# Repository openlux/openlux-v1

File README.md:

This is the first version of this camera and had a few small design issues, these will be fixed in v2.

# openlux

openlux is an open source design for an astrophotography camera designed around the KAI-11002 CCD sensor.

### Hardware specifications

* 4-layer PCB

* KAI-11002 CCD sensor
  * 4008x2672 resolution
  * 43.3mm diagonal size
  * 9um pixels
  * Interline transfer
  * Electronic shutter

* AD9826 ADC
  * Correlated double sampling
  * 16-bit

* ATmega328P + FT2232H
  * High speed USB 2.0 (480Mb/s)

### Sample photo

* 32x 5min lights (2hrs 40mins total), 16x darks, 16x flats, 16x dark flats
* AT65EDQ + HEQ5
* ST80 & ASI174MM for guiding

### PCB render

### Photos

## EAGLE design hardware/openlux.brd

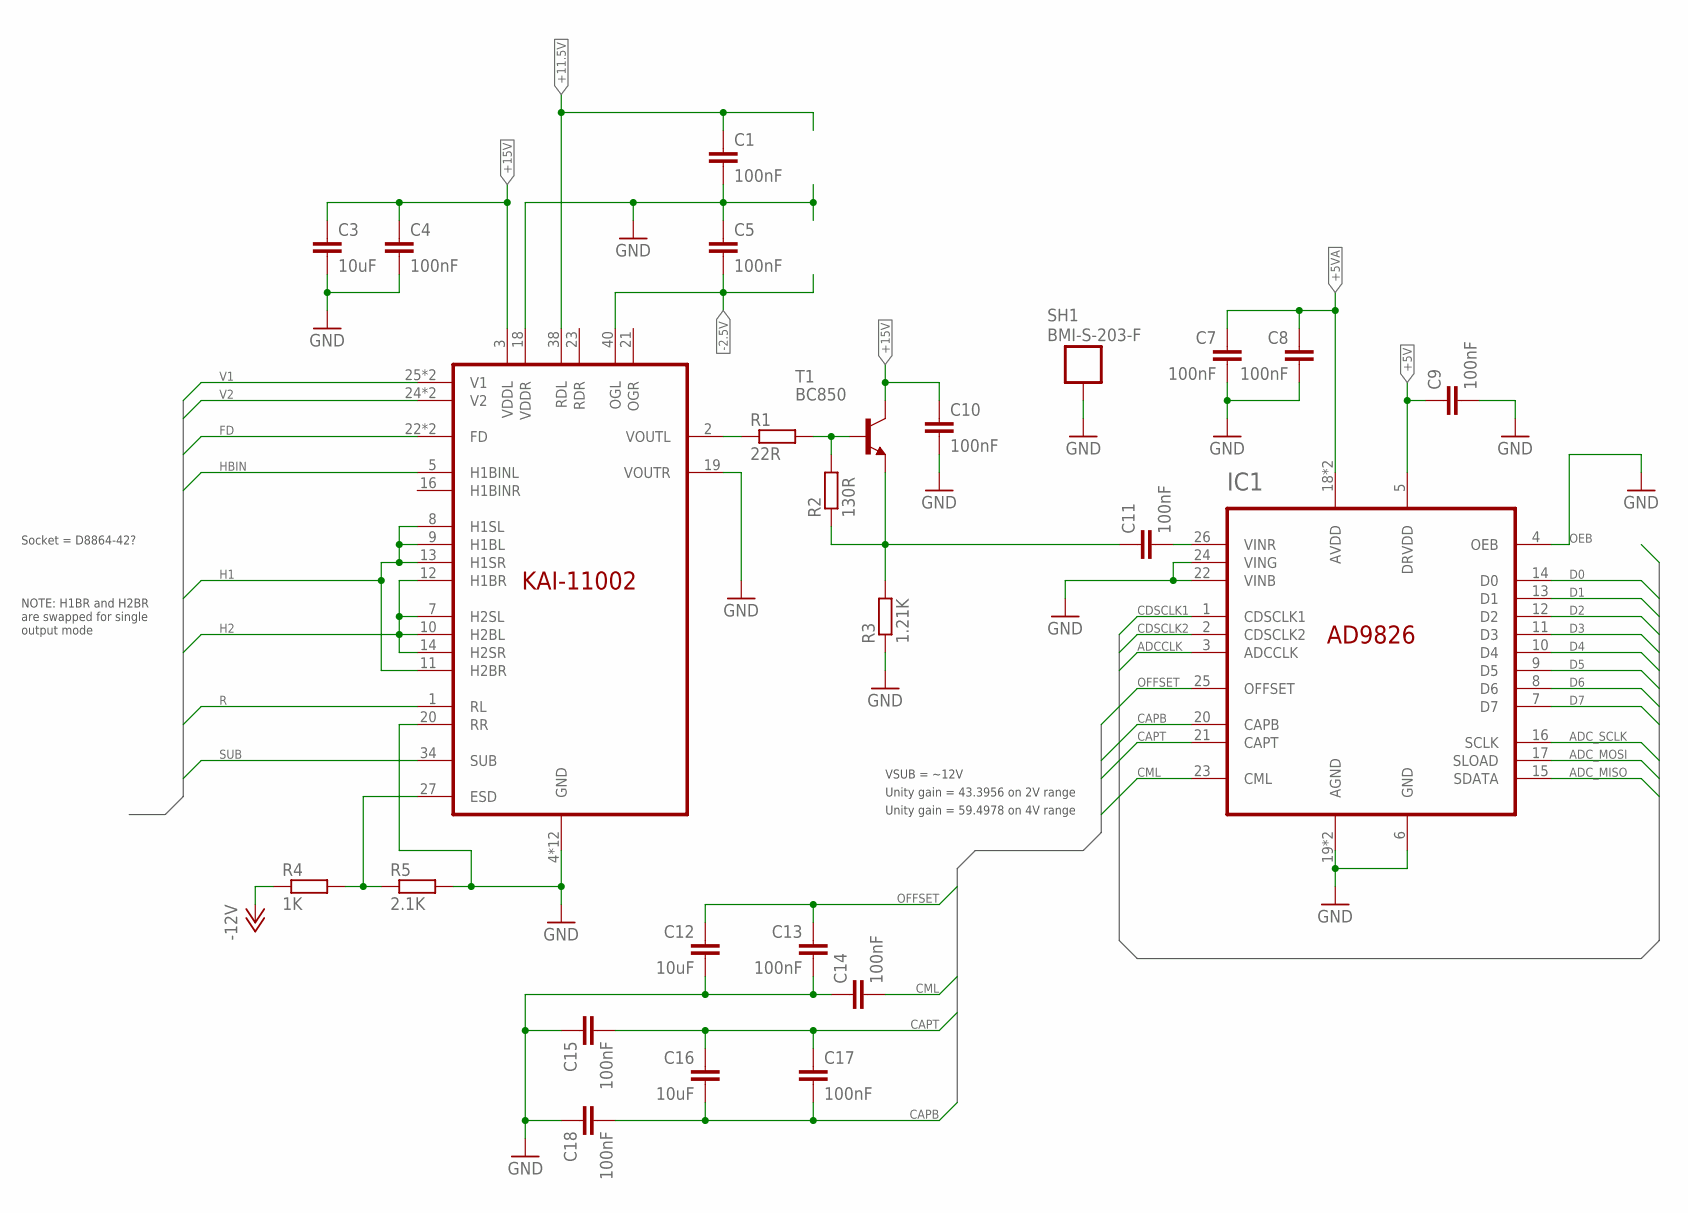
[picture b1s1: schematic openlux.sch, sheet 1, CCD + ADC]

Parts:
C1, C4, C5, C7, C8, C9, C10, C11, C13, C14, C15, C17, C18: 100nF; 0603
C3, C12, C16: 10uF; 0805
IC1: AD9826; SSOP28
IS1: KAI-11002
R1: 22R; 0603
R2: 130R; 0603
R3: 1.21K; 0603
R4: 1K; 0603
R5: 2.1K; 0603
SH1: BMI-S-203-F
T1: BC850; SOT23

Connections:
+5V: C9.1, IC1.5 (DRVDD); also elsewhere on the board
+5VA: C7.1, C8.1, IC1.18 (AVDD), IC1.28 (AVDD); also elsewhere on the board
+11.5V: C1.1, IS1.38 (RDL); also elsewhere on the board
+15V: C3.1, C4.1, C10.1, IS1.3 (VDDL), T1.3 (C); also elsewhere on the board
-2.5V: C5.2, IS1.40 (OGL); also elsewhere on the board
-12V: R4.1; also elsewhere on the board
ADCCLK: IC1.3 (ADCCLK); also elsewhere on the board
ADC_MISO: IC1.15 (SDATA)
ADC_MOSI: IC1.17 (SLOAD)
ADC_SCLK: IC1.16 (SCLK)
CAPB: C16.2, C17.2, C18.2, IC1.20 (CAPB)
CAPT: C15.2, C16.1, C17.1, IC1.21 (CAPT)
CDSCLK1: IC1.1 (CDSCLK1); also elsewhere on the board
CDSCLK2: IC1.2 (CDSCLK2); also elsewhere on the board
CML: C14.2, IC1.23 (CML)
D0: IC1.14 (D0); also elsewhere on the board
D1: IC1.13 (D1); also elsewhere on the board
D2: IC1.12 (D2); also elsewhere on the board
D3: IC1.11 (D3); also elsewhere on the board
D4: IC1.10 (D4); also elsewhere on the board
D5: IC1.9 (D5); also elsewhere on the board
D6: IC1.8 (D6); also elsewhere on the board
D7: IC1.7 (D7); also elsewhere on the board
FD: IS1.22 (FD), IS1.39 (FD); also elsewhere on the board
GND: C1.2, C3.2, C4.2, C5.1, C7.2, C8.2, C9.2, C10.2, C12.2, C13.2, C14.1, C15.1, C18.1, IC1.4 (OEB), IC1.6 (GND), IC1.19 (AGND), IC1.22 (VINB), IC1.24 (VING), IC1.27 (AGND), IS1.4 (GND), IS1.6 (GND), IS1.15 (GND), IS1.17 (GND), IS1.18 (VDDR), IS1.19 (VOUTR), IS1.20 (RR), IS1.26 (GND), IS1.28 (GND), IS1.29 (GND), IS1.30 (GND), IS1.31 (GND), IS1.32 (GND), IS1.33 (GND), IS1.35 (GND), R3.1, R5.2, SH1.P$1, SH1.P$2, SH1.P$3, SH1.P$4, SH1.P$5, SH1.P$6, SH1.P$7, SH1.P$8, SH1.P$9, SH1.P$10, SH1.P$11, SH1.P$12, SH1.P$13, SH1.P$14, SH1.P$15, SH1.P$19, SH1.P$20; also elsewhere on the board
H1: IS1.8 (H1SL), IS1.9 (H1BL), IS1.11 (H2BR), IS1.13 (H1SR); also elsewhere on the board
H2: IS1.7 (H2SL), IS1.10 (H2BL), IS1.12 (H1BR), IS1.14 (H2SR); also elsewhere on the board
HBIN: IS1.5 (H1BINL); also elsewhere on the board
unnamed: R1.2, R2.2, T1.1 (B)
unnamed: C11.2, IC1.26 (VINR)
unnamed: IS1.2 (VOUTL), R1.1
OFFSET: C12.1, C13.1, IC1.25 (OFFSET)
R: IS1.1 (RL); also elsewhere on the board
SUB: IS1.34 (SUB); also elsewhere on the board
V1: IS1.25 (V1), IS1.37 (V1); also elsewhere on the board
V2: IS1.24 (V2), IS1.36 (V2); also elsewhere on the board
VESD: IS1.27 (ESD), R4.2, R5.1
VOUT: C11.1, R2.1, R3.2, T1.2 (E)

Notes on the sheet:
NOTE: H1BR and H2BR are swapped for single output mode
Unity gain = 43.3956 on 2V range
Unity gain = 59.4978 on 4V range
Socket = D8864-42?
VSUB = ~12V

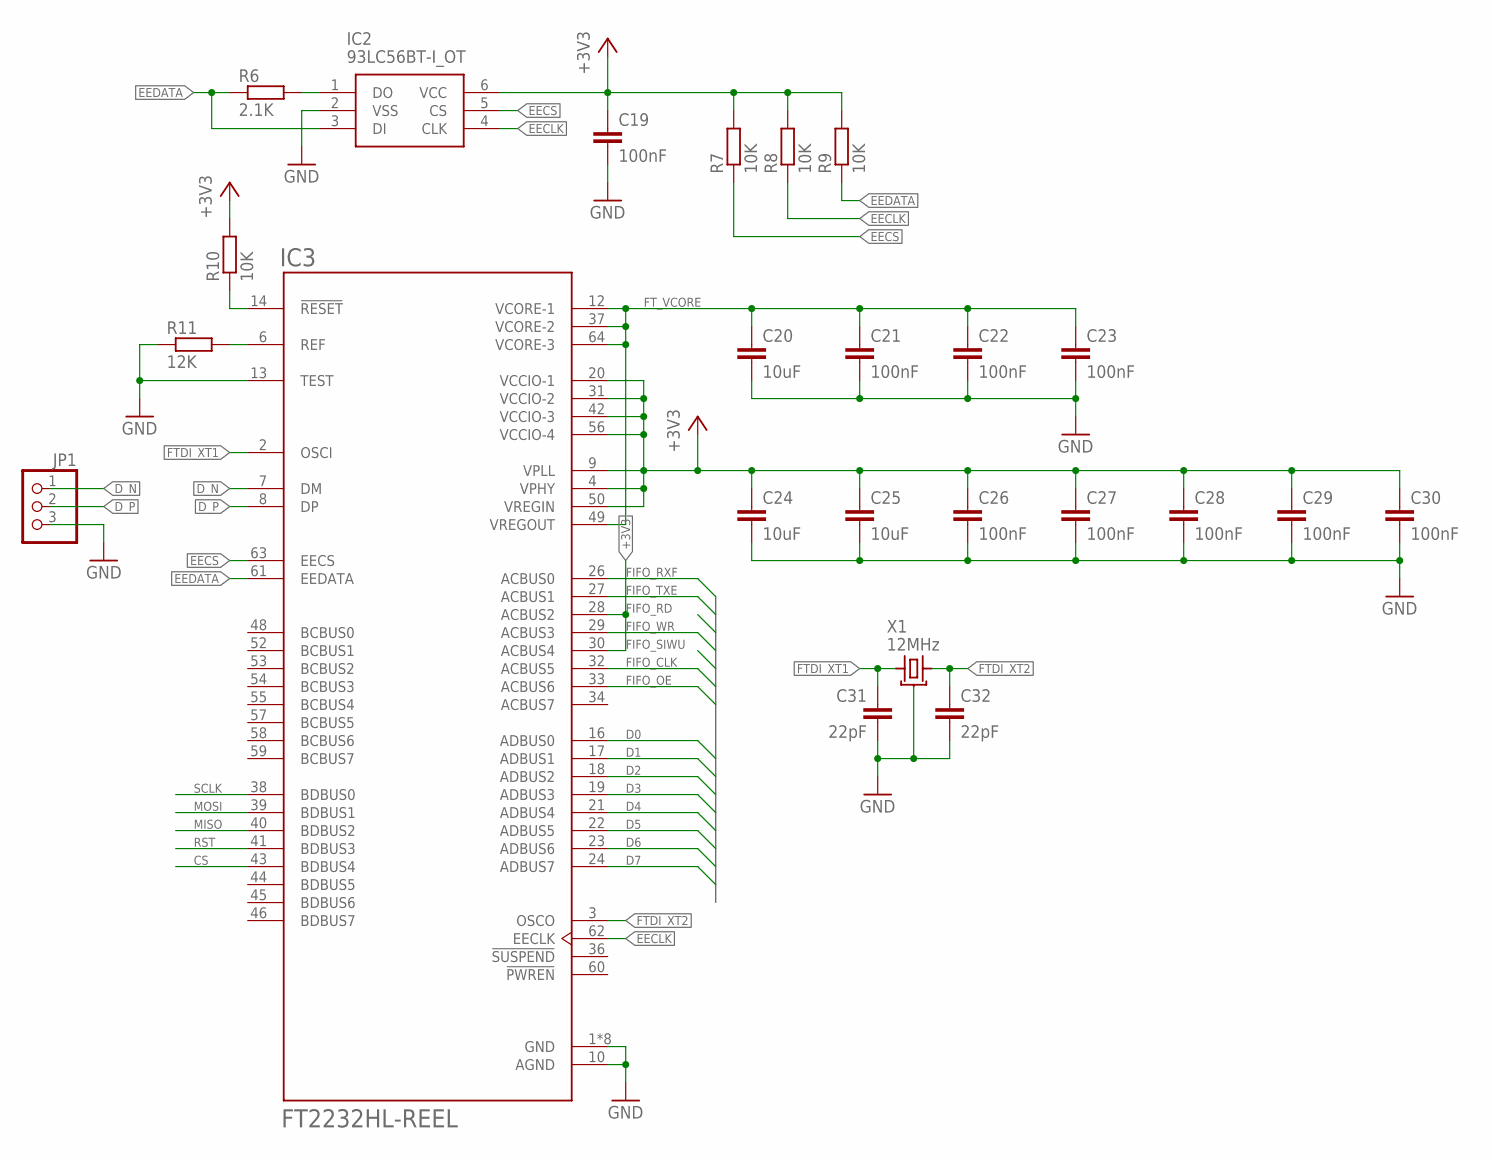
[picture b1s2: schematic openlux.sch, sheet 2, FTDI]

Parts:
C19, C21, C22, C23, C26, C27, C28, C29, C30: 100nF; 0603
C20, C24, C25: 10uF; 0805
C31, C32: 22pF; 0603
IC2: 93LC56BT-I_OT; SOT95P270X145-6N
IC3: FT2232HL-REEL; QFP50P1200X1200X160-64N
JP1: PINHD-1X3; 1X03
R6: 2.1K; 0603
R7, R8, R9, R10: 10K; 0603
R11: 12K; 0603
X1: 12MHz; 3.2X2.5_4

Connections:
+3V3: C19.1, C24.1, C25.1, C26.1, C27.1, C28.1, C29.1, C30.1, IC2.6 (VCC), IC3.4 (VPHY), IC3.9 (VPLL), IC3.20 (VCCIO-1), IC3.28 (ACBUS2), IC3.30 (ACBUS4), IC3.31 (VCCIO-2), IC3.42 (VCCIO-3), IC3.50 (VREGIN), IC3.56 (VCCIO-4), R7.2, R8.2, R9.2, R10.2; also elsewhere on the board
CS: IC3.43 (BDBUS4); also elsewhere on the board
D0: IC3.16 (ADBUS0); also elsewhere on the board
D1: IC3.17 (ADBUS1); also elsewhere on the board
D2: IC3.18 (ADBUS2); also elsewhere on the board
D3: IC3.19 (ADBUS3); also elsewhere on the board
D4: IC3.21 (ADBUS4); also elsewhere on the board
D5: IC3.22 (ADBUS5); also elsewhere on the board
D6: IC3.23 (ADBUS6); also elsewhere on the board
D7: IC3.24 (ADBUS7); also elsewhere on the board
D_N: IC3.7 (DM), JP1.1
D_P: IC3.8 (DP), JP1.2
EECLK: IC2.4 (CLK), IC3.62 (EECLK), R8.1
EECS: IC2.5 (CS), IC3.63 (EECS), R7.1
EEDATA: IC2.3 (DI), IC3.61 (EEDATA), R6.1, R9.1
FIFO_CLK: IC3.32 (ACBUS5)
FIFO_OE: IC3.33 (ACBUS6)
FIFO_RXF: IC3.26 (ACBUS0)
FIFO_TXE: IC3.27 (ACBUS1); also elsewhere on the board
FIFO_WR: IC3.29 (ACBUS3); also elsewhere on the board
FTDI_XT1: C31.1, IC3.2 (OSCI), X1.P$1 (XT1)
FTDI_XT2: C32.1, IC3.3 (OSCO), X1.P$3 (XT2)
FT_VCORE: C20.1, C21.1, C22.1, C23.1, IC3.12 (VCORE-1), IC3.37 (VCORE-2), IC3.49 (VREGOUT), IC3.64 (VCORE-3)
GND: C19.2, C20.2, C21.2, C22.2, C23.2, C24.2, C25.2, C26.2, C27.2, C28.2, C29.2, C30.2, C31.2, C32.2, IC2.2 (VSS), IC3.1 (GND), IC3.5 (GND), IC3.10 (AGND), IC3.11 (GND), IC3.13 (TEST), IC3.15 (GND), IC3.25 (GND), IC3.35 (GND), IC3.47 (GND), IC3.51 (GND), JP1.3, R11.1, X1.P$2 (GND), X1.P$4 (GND); also elsewhere on the board
MISO: IC3.40 (BDBUS2); also elsewhere on the board
MOSI: IC3.39 (BDBUS1); also elsewhere on the board
unnamed: IC3.6 (REF), R11.2
unnamed: IC2.1 (DO), R6.2
unnamed: IC3.14 (!RESET), R10.1
RST: IC3.41 (BDBUS3); also elsewhere on the board
SCLK: IC3.38 (BDBUS0); also elsewhere on the board

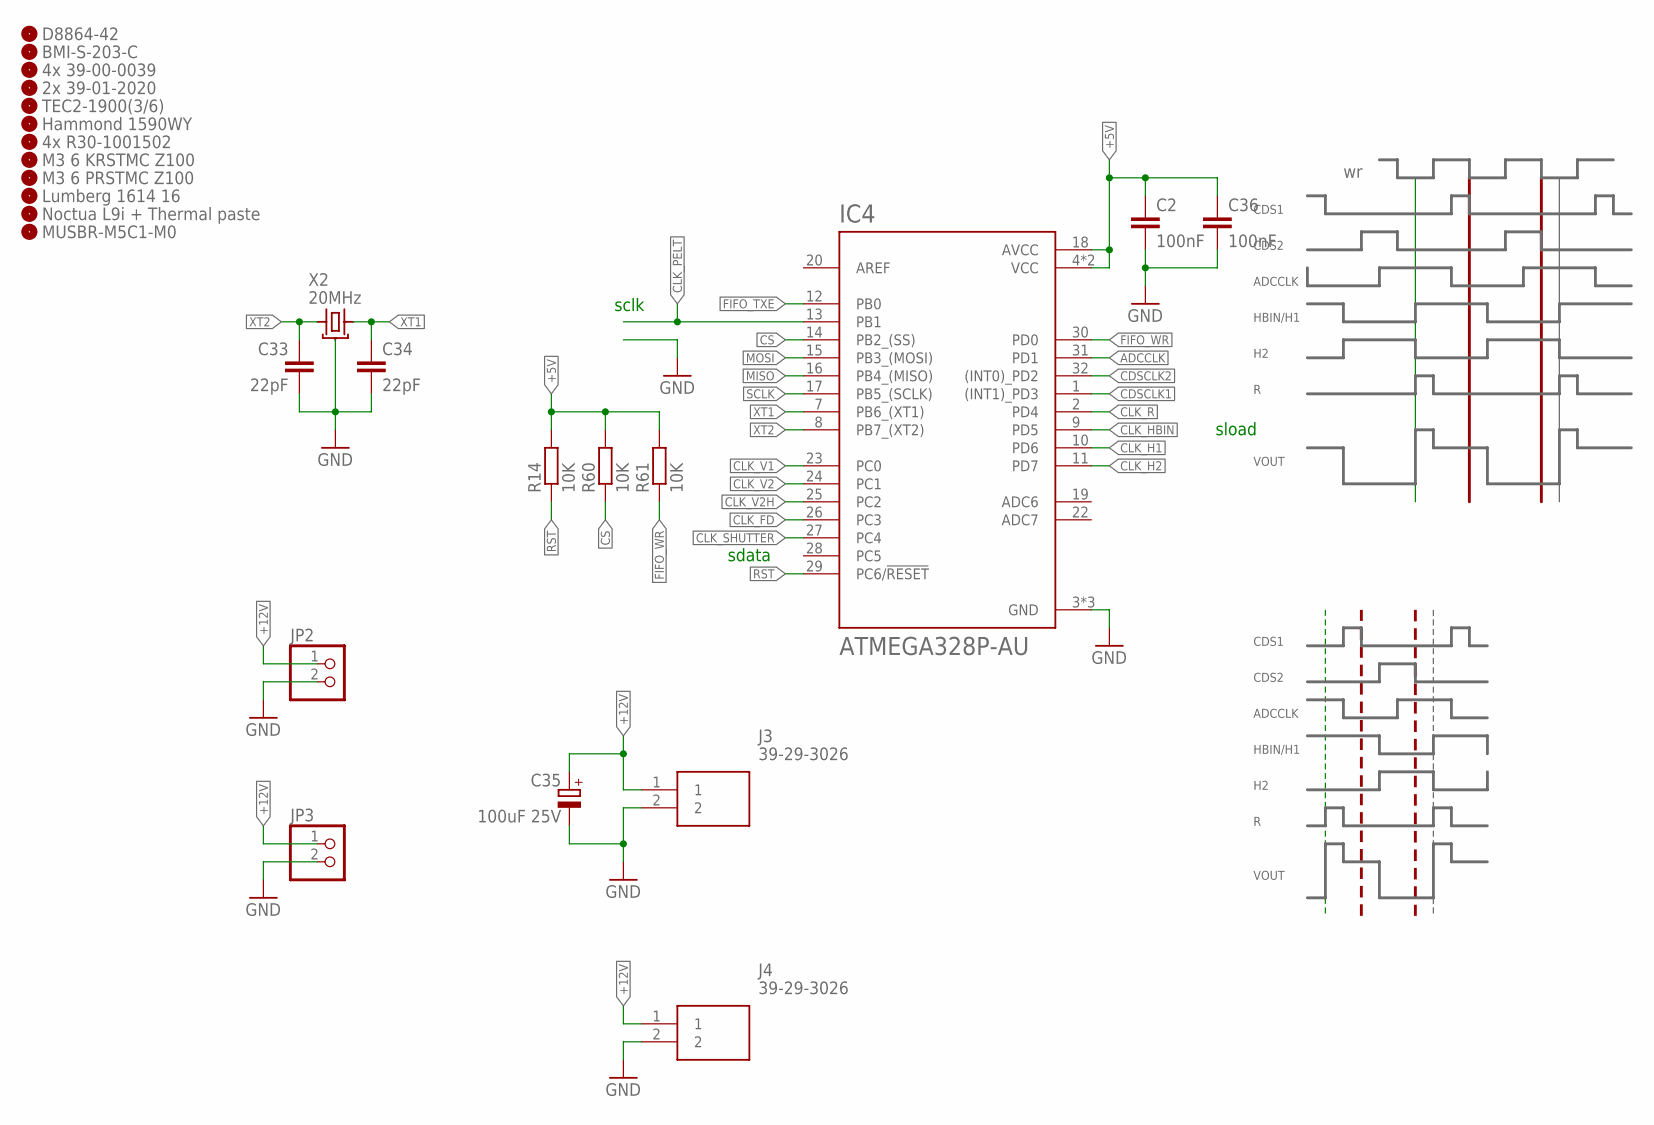
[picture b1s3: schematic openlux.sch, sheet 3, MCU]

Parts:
C2, C36: 100nF; 0603
C33, C34: 22pF; 0603
C35: 100uF 25V; E2,5-6
EXTRA1: 4x R30-1001502; EMPTY
EXTRA2: Hammond 1590WY; EMPTY
EXTRA3: M3 6 KRSTMC Z100; EMPTY
EXTRA4: M3 6 PRSTMC Z100; EMPTY
EXTRA5: TEC2-1900(3/6); EMPTY
EXTRA6: 2x 39-01-2020; EMPTY
EXTRA7: 4x 39-00-0039; EMPTY
EXTRA8: Lumberg 1614 16; EMPTY
EXTRA9: Noctua L9i + Thermal paste; EMPTY
EXTRA10: MUSBR-M5C1-M0; EMPTY
EXTRA11: BMI-S-203-C; EMPTY
EXTRA12: D8864-42; EMPTY
IC4: ATMEGA328P-AU; QFP80P900X900X120-32N
J3, J4: 39-29-3026; SHDR2W125P0X550_1X2_960X540X13
JP2: PINHD-1X2; 1X02
JP3: PINHD-1X2/90; 1X02/90
R14, R60, R61: 10K; 0603
X2: 20MHz; 3.2X2.5_4

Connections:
+5V: C2.1, C36.1, IC4.4 (VCC), IC4.6 (VCC), IC4.18 (AVCC), R14.2, R60.2, R61.2; also elsewhere on the board
+12V: C35.+, J3.1, J4.1, JP2.1, JP3.1; also elsewhere on the board
ADCCLK: IC4.31 (PD1); also elsewhere on the board
CDSCLK1: IC4.1 ((INT1)_PD3); also elsewhere on the board
CDSCLK2: IC4.32 ((INT0)_PD2); also elsewhere on the board
CLK_FD: IC4.26 (PC3); also elsewhere on the board
CLK_H1: IC4.10 (PD6); also elsewhere on the board
CLK_H2: IC4.11 (PD7); also elsewhere on the board
CLK_HBIN: IC4.9 (PD5); also elsewhere on the board
CLK_PELT: IC4.13 (PB1)
CLK_R: IC4.2 (PD4); also elsewhere on the board
CLK_SHUTTER: IC4.27 (PC4); also elsewhere on the board
CLK_V1: IC4.23 (PC0); also elsewhere on the board
CLK_V2: IC4.24 (PC1); also elsewhere on the board
CLK_V2H: IC4.25 (PC2); also elsewhere on the board
CS: IC4.14 (PB2_(SS)), R60.1; also elsewhere on the board
FIFO_TXE: IC4.12 (PB0); also elsewhere on the board
FIFO_WR: IC4.30 (PD0), R61.1; also elsewhere on the board
GND: C2.2, C33.2, C34.2, C35.-, C36.2, IC4.3 (GND), IC4.5 (GND), IC4.21 (GND), J3.2, J4.2, JP2.2, JP3.2, X2.P$2 (GND), X2.P$4 (GND); also elsewhere on the board
MISO: IC4.16 (PB4_(MISO)); also elsewhere on the board
MOSI: IC4.15 (PB3_(MOSI)); also elsewhere on the board
RST: IC4.29 (PC6/!RESET), R14.1; also elsewhere on the board
SCLK: IC4.17 (PB5_(SCLK)); also elsewhere on the board
XT1: C34.1, IC4.7 (PB6_(XT1)), X2.P$3 (XT2)
XT2: C33.1, IC4.8 (PB7_(XT2)), X2.P$1 (XT1)

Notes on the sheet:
HBIN/H1
ADCCLK
CDS1
CDS2
VOUT
sload
sclk
sdata

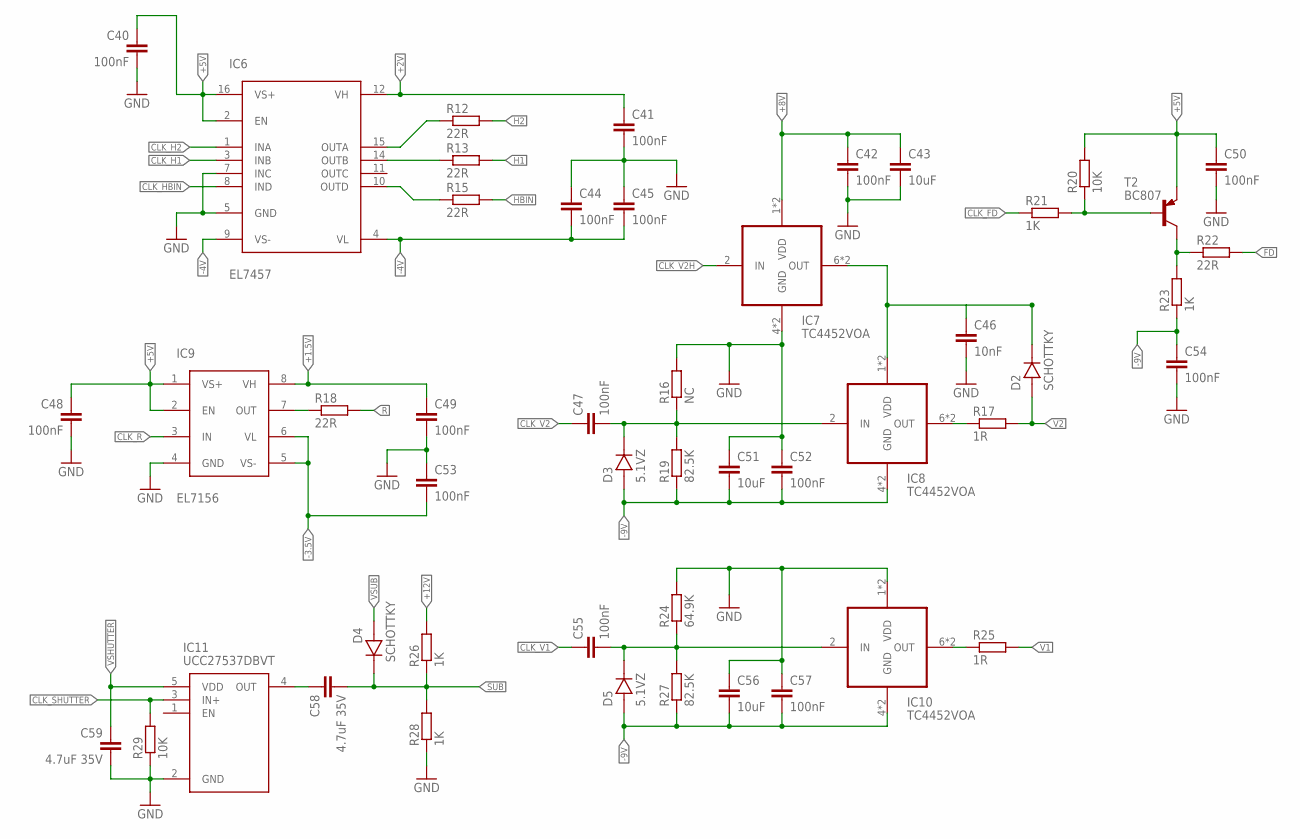
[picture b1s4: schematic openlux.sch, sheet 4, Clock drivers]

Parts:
C40, C41, C42, C44, C45, C47, C48, C49, C50, C52, C53, C54, C55, C57: 100nF; 0603
C43, C51, C56: 10uF; 0805
C46: 10nF; 0603
C58, C59: 4.7uF 35V; 0805
D2, D4: SCHOTTKY; SOD523
D3, D5: 5.1VZ; SOD523
IC6: EL7457; QSOP16
IC7, IC8, IC10: TC4452VOA; SOIC8
IC9: EL7156; SOIC8
IC11: UCC27537DBVT; SOT95P280X145-5N
R12, R13, R15, R18, R22: 22R; 0603
R16: NC; 0603
R17, R25: 1R; 0603
R19, R27: 82.5K; 0603
R20, R29: 10K; 0603
R21, R23, R26, R28: 1K; 0603
R24: 64.9K; 0603
T2: BC807; SOT23-BEC

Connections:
+1.5V: C49.1, IC9.8 (VH); also elsewhere on the board
+2V: C41.1, IC6.12 (VH); also elsewhere on the board
+5V: C40.1, C48.1, C50.1, IC6.2 (EN), IC6.16 (VS+), IC9.1 (VS+), IC9.2 (EN), R20.2, T2.E; also elsewhere on the board
+8V: C42.1, C43.1, IC7.1 (VDD), IC7.8 (VDD); also elsewhere on the board
+12V: R26.2; also elsewhere on the board
-3.5V: C53.2, IC9.5 (VS-), IC9.6 (VL); also elsewhere on the board
-4V: C44.2, C45.2, IC6.4 (VL), IC6.9 (VS-); also elsewhere on the board
-9V: C51.2, C52.2, C54.1, C56.2, C57.2, D3.1, D5.1, IC8.4 (GND), IC8.5 (GND), IC10.4 (GND), IC10.5 (GND), R19.1, R23.1, R27.1; also elsewhere on the board
CLK_FD: R21.1; also elsewhere on the board
CLK_H1: IC6.3 (INB); also elsewhere on the board
CLK_H2: IC6.1 (INA); also elsewhere on the board
CLK_HBIN: IC6.8 (IND); also elsewhere on the board
CLK_R: IC9.3 (IN); also elsewhere on the board
CLK_SHUTTER: IC11.3 (IN+), R29.2; also elsewhere on the board
CLK_V1: C55.1; also elsewhere on the board
CLK_V2: C47.1; also elsewhere on the board
CLK_V2H: IC7.2 (IN); also elsewhere on the board
FD: R22.2; also elsewhere on the board
GND: C40.2, C41.2, C42.2, C43.2, C44.1, C45.1, C46.2, C48.2, C49.2, C50.2, C51.1, C52.1, C53.1, C54.2, C56.1, C57.1, C59.2, IC6.5 (GND), IC6.7 (INC), IC7.4 (GND), IC7.5 (GND), IC9.4 (GND), IC10.1 (VDD), IC10.8 (VDD), IC11.2 (GND), R16.2, R24.2, R28.1, R29.1; also elsewhere on the board
H1: R13.2; also elsewhere on the board
H2: R12.2; also elsewhere on the board
HBIN: R15.2; also elsewhere on the board
unnamed: IC9.7 (OUT), R18.1
unnamed: C47.2, D3.2, IC8.2 (IN), R16.1, R19.2
unnamed: C58.1, IC11.4 (OUT)
unnamed: IC6.14 (OUTB), R13.1
unnamed: IC6.15 (OUTA), R12.1
unnamed: IC6.10 (OUTD), R15.1
unnamed: C55.2, D5.2, IC10.2 (IN), R24.1, R27.2
unnamed: R22.1, R23.2, T2.C
unnamed: R20.1, R21.2, T2.B
R: R18.2; also elsewhere on the board
SUB: C58.2, D4.2, R26.1, R28.2; also elsewhere on the board
V1: R25.2; also elsewhere on the board
V1P: IC10.6 (OUT), IC10.7 (OUT), R25.1
V2: D2.1, R17.2; also elsewhere on the board
V2H: C46.1, D2.2, IC7.6 (OUT), IC7.7 (OUT), IC8.1 (VDD), IC8.8 (VDD)
V2P: IC8.6 (OUT), IC8.7 (OUT), R17.1
VSHUTTER: C59.1, IC11.5 (VDD); also elsewhere on the board
VSUB: D4.1; also elsewhere on the board

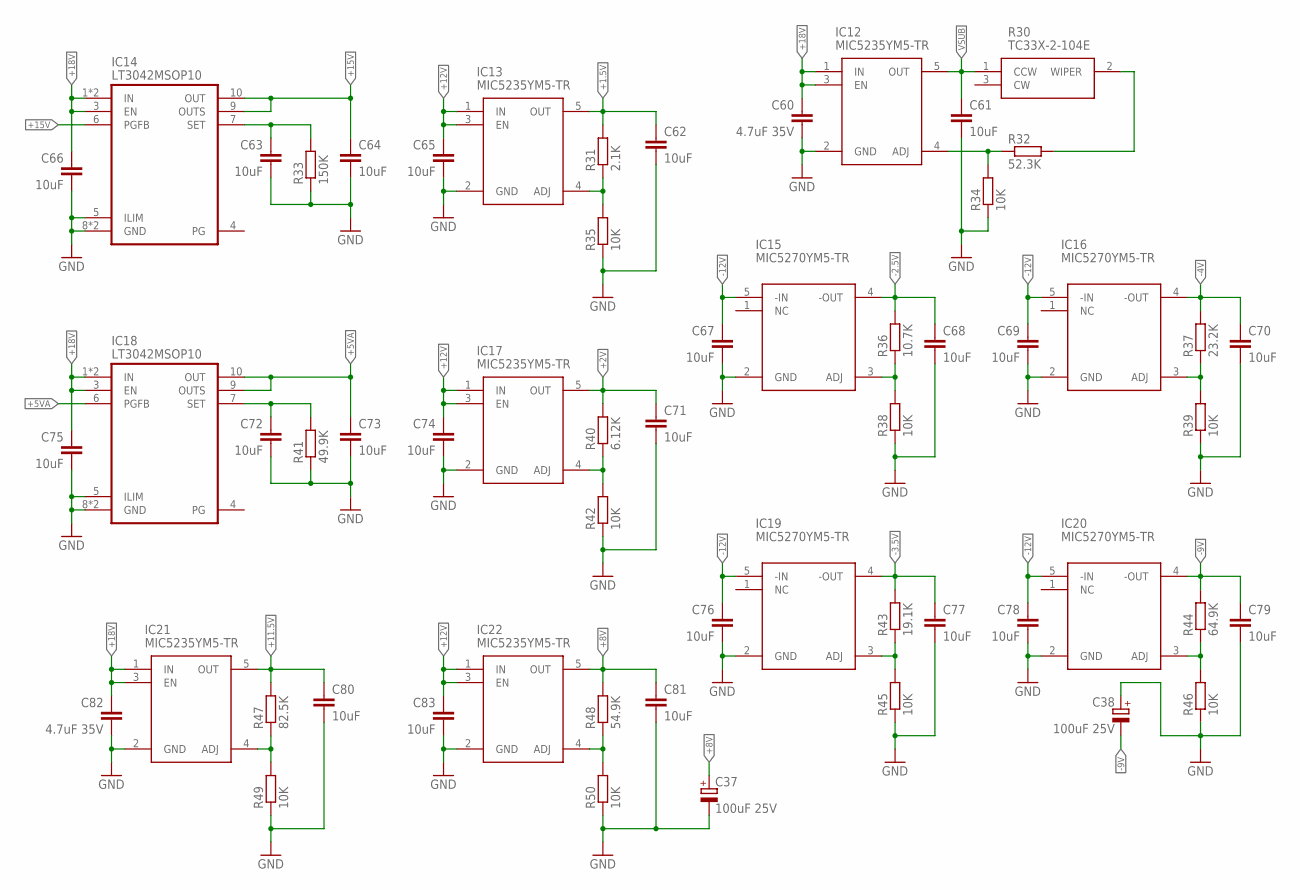
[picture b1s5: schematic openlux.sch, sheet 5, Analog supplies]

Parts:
C37, C38: 100uF 25V; E2,5-6
C60, C82: 4.7uF 35V; 0805
C61, C62, C63, C64, C65, C66, C67, C68, C69, C70, C71, C72, C73, C74, C75, C76, C77, C78, C79, C80, C81, C83: 10uF; 0805
IC12, IC13, IC17, IC21, IC22: MIC5235YM5-TR; SOT95P280X145-5N
IC14, IC18: LT3042MSOP10; MSOP10
IC15, IC16, IC19, IC20: MIC5270YM5-TR; SOT95P280X145-5N
R30: TC33X-2-104E; TC33X2
R31: 2.1K; 0603
R32: 52.3K; 0603
R33: 150K; 0603
R34, R35, R38, R39, R42, R45, R46, R49, R50: 10K; 0603
R36: 10.7K; 0603
R37: 23.2K; 0603
R40: 6.12K; 0603
R41: 49.9K; 0603
R43: 19.1K; 0603
R44: 64.9K; 0603
R47: 82.5K; 0603
R48: 54.9K; 0603

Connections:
+1.5V: C62.1, IC13.5 (OUT), R31.2; also elsewhere on the board
+2V: C71.1, IC17.5 (OUT), R40.2; also elsewhere on the board
+5VA: C73.1, IC18.6 (PGFB), IC18.9 (OUTS), IC18.10 (OUT); also elsewhere on the board
+8V: C37.+, C81.1, IC22.5 (OUT), R48.2; also elsewhere on the board
+11.5V: C80.1, IC21.5 (OUT), R47.2; also elsewhere on the board
+12V: C65.1, C74.1, C83.1, IC13.1 (IN), IC13.3 (EN), IC17.1 (IN), IC17.3 (EN), IC22.1 (IN), IC22.3 (EN); also elsewhere on the board
+15V: C64.1, IC14.6 (PGFB), IC14.9 (OUTS), IC14.10 (OUT); also elsewhere on the board
+18V: C60.1, C66.1, C75.1, C82.1, IC12.1 (IN), IC12.3 (EN), IC14.1 (IN), IC14.2 (IN), IC14.3 (EN), IC18.1 (IN), IC18.2 (IN), IC18.3 (EN), IC21.1 (IN), IC21.3 (EN); also elsewhere on the board
-2.5V: C68.1, IC15.4 (-OUT), R36.2; also elsewhere on the board
-3.5V: C77.1, IC19.4 (-OUT), R43.2; also elsewhere on the board
-4V: C70.1, IC16.4 (-OUT), R37.2; also elsewhere on the board
-9V: C38.-, C79.1, IC20.4 (-OUT), R44.2; also elsewhere on the board
-12V: C67.1, C69.1, C76.1, C78.1, IC15.5 (-IN), IC16.5 (-IN), IC19.5 (-IN), IC20.5 (-IN); also elsewhere on the board
GND: C37.-, C38.+, C60.2, C61.2, C62.2, C63.2, C64.2, C65.2, C66.2, C67.2, C68.2, C69.2, C70.2, C71.2, C72.2, C73.2, C74.2, C75.2, C76.2, C77.2, C78.2, C79.2, C80.2, C81.2, C82.2, C83.2, IC12.2 (GND), IC13.2 (GND), IC14.5 (ILIM), IC14.8 (GND), IC14.EP (GND), IC15.2 (GND), IC16.2 (GND), IC17.2 (GND), IC18.5 (ILIM), IC18.8 (GND), IC18.EP (GND), IC19.2 (GND), IC20.2 (GND), IC21.2 (GND), IC22.2 (GND), R33.1, R34.1, R35.1, R38.1, R39.1, R41.1, R42.1, R45.1, R46.1, R49.1, R50.1; also elsewhere on the board
unnamed: IC20.3 (ADJ), R44.1, R46.2
unnamed: IC22.4 (ADJ), R48.1, R50.2
unnamed: IC13.4 (ADJ), R31.1, R35.2
unnamed: IC19.3 (ADJ), R43.1, R45.2
unnamed: IC12.4 (ADJ), R32.1, R34.2
unnamed: IC16.3 (ADJ), R37.1, R39.2
unnamed: IC15.3 (ADJ), R36.1, R38.2
unnamed: IC17.4 (ADJ), R40.1, R42.2
unnamed: R30.2 (WIPER), R32.2
unnamed: C63.1, IC14.7 (SET), R33.2
unnamed: IC21.4 (ADJ), R47.1, R49.2
unnamed: C72.1, IC18.7 (SET), R41.2
VSUB: C61.1, IC12.5 (OUT), R30.1 (CCW); also elsewhere on the board

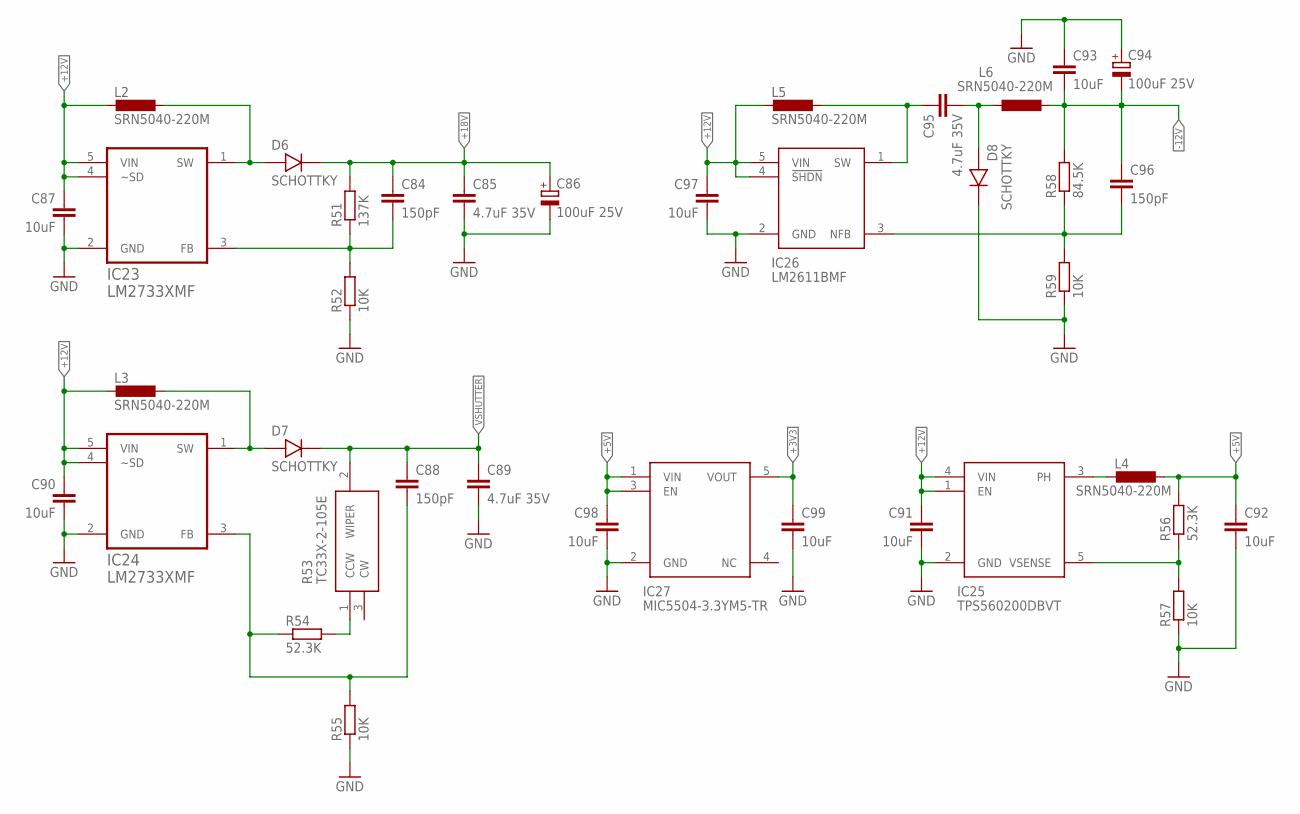
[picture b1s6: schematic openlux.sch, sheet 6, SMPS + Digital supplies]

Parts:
C84, C88, C96: 150pF; 0603
C85, C89, C95: 4.7uF 35V; 0805
C86, C94: 100uF 25V; E2,5-6
C87, C90, C91, C92, C93, C97, C98, C99: 10uF; 0805
D6, D7, D8: SCHOTTKY; SOD523
IC23, IC24: LM2733XMF; SOT95P284X119-5N
IC25: TPS560200DBVT; SOT95P280X145-5N
IC26: LM2611BMF; SOT95P280X145-5N
IC27: MIC5504-3.3YM5-TR; SOT95P280X130-5N
L2, L3, L4, L5, L6: SRN5040-220M; 5X5_2
R51: 137K; 0603
R52, R55, R57, R59: 10K; 0603
R53: TC33X-2-105E; TC33X2
R54, R56: 52.3K; 0603
R58: 84.5K; 0603

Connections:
18VSH: D6.1, IC23.1 (SW), L2.P$1 (1)
+3V3: C99.1, IC27.5 (VOUT); also elsewhere on the board
+5V: C92.1, C98.1, IC27.1 (VIN), IC27.3 (EN), L4.P$1 (1), R56.2; also elsewhere on the board
+12V: C87.1, C90.1, C91.1, C97.1, IC23.4 (~SD), IC23.5 (VIN), IC24.4 (~SD), IC24.5 (VIN), IC25.1 (EN), IC25.4 (VIN), IC26.4 (!SHDN), IC26.5 (VIN), L2.P$2 (2), L3.P$2 (2), L5.P$2 (2); also elsewhere on the board
+18V: C84.1, C85.1, C86.+, D6.2, R51.2; also elsewhere on the board
-12V: C93.2, C94.-, C96.1, L6.P$1 (1), R58.2; also elsewhere on the board
-12V_SW: C95.1, IC26.1 (SW), L5.P$1 (1)
-12V_SWB: C95.2, D8.1, L6.P$2 (2)
GND: C85.2, C86.-, C87.2, C89.2, C90.2, C91.2, C92.2, C93.1, C94.+, C97.2, C98.2, C99.2, D8.2, IC23.2 (GND), IC24.2 (GND), IC25.2 (GND), IC26.2 (GND), IC27.2 (GND), R52.1, R55.1, R57.1, R59.1; also elsewhere on the board
unnamed: C96.2, IC26.3 (NFB), R58.1, R59.2
unnamed: R53.1 (CCW), R54.2
unnamed: C88.2, IC24.3 (FB), R54.1, R55.2
unnamed: IC25.3 (PH), L4.P$2 (2)
unnamed: IC25.5 (VSENSE), R56.1, R57.2
unnamed: C84.2, IC23.3 (FB), R51.1, R52.2
VSHTVSH: D7.1, IC24.1 (SW), L3.P$1 (1)
VSHUTTER: C88.1, C89.1, D7.2, R53.2 (WIPER); also elsewhere on the board

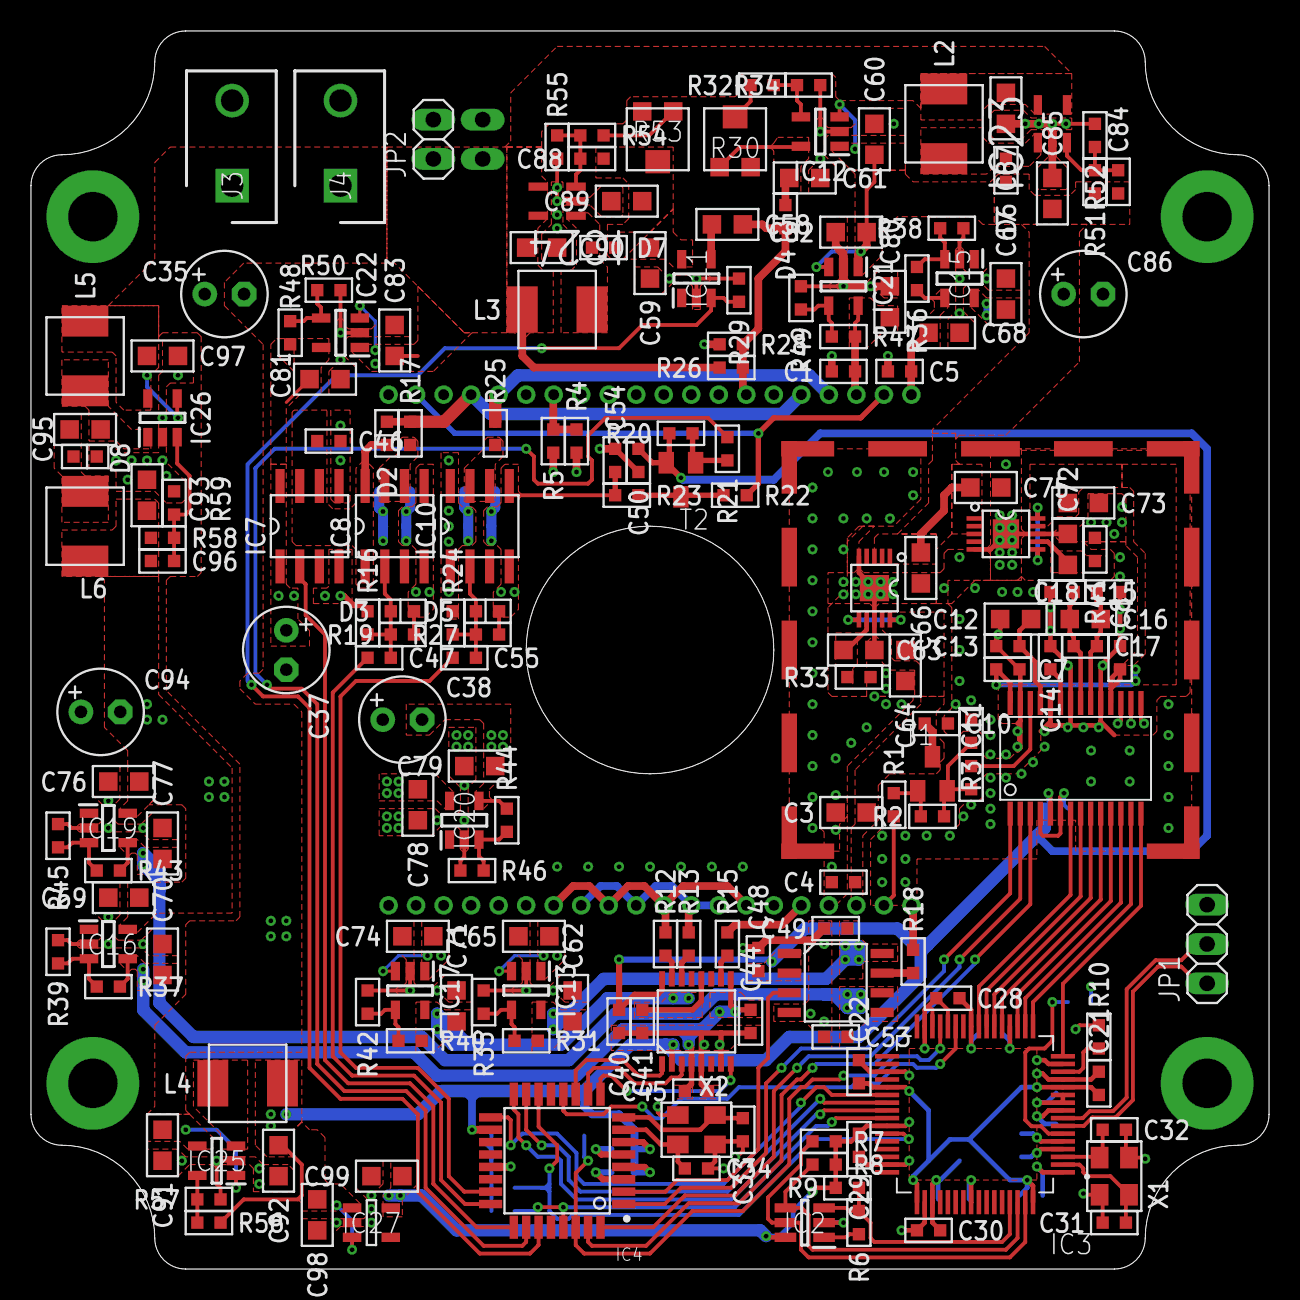
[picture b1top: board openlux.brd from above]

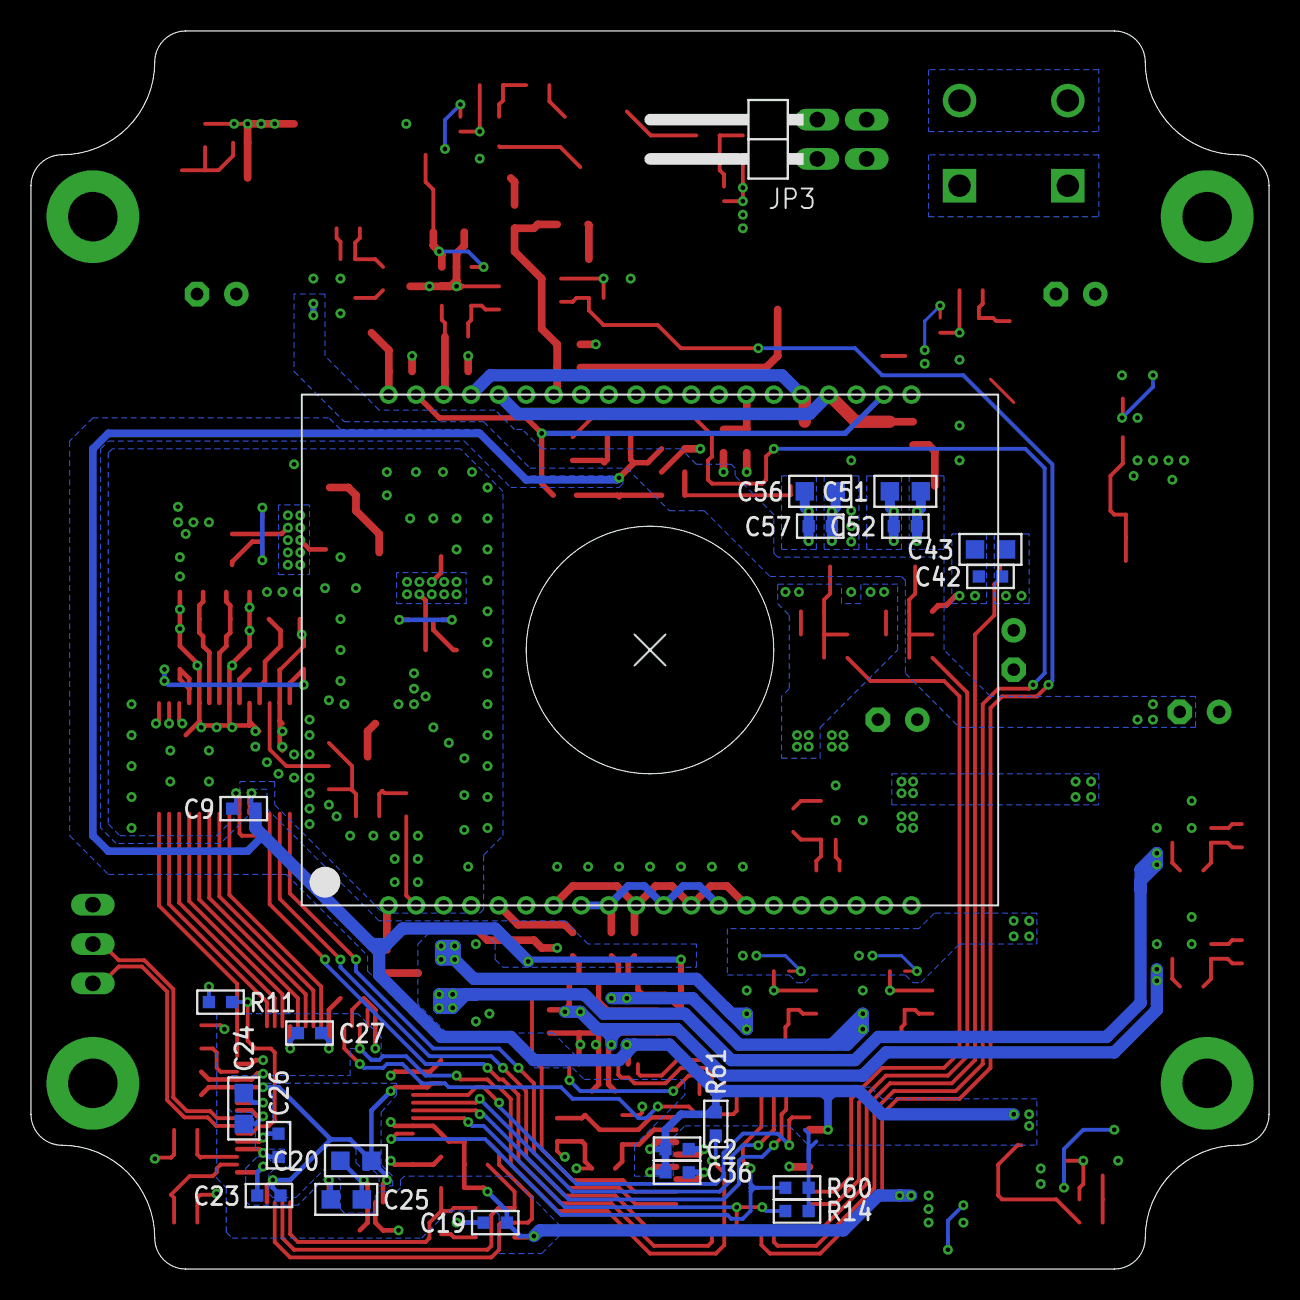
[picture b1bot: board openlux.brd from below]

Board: 4 copper layers, 80.0 x 80.0 mm, 219 parts (22 on the bottom side), 109 nets.

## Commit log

2022-04-18 Add readme
2022-04-18 Update readme to fix image extension
2022-04-18 Fix readme header
2022-04-18 Fix readme typo
2022-04-18 Add sample photo details to readme
